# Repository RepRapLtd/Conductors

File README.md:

# Conductors
Experiments with 3D printing conducting filament

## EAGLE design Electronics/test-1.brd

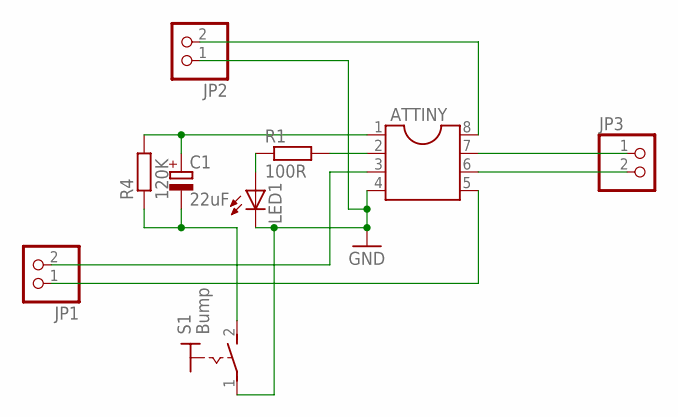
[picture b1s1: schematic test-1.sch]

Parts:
ATTINY: DIL8; DIL08
C1: 22uF; E3,5-8
JP1, JP2, JP3: PINHD-1X2; 1X02
LED1: LED3MM
R1: 100R; 0204/7
R4: 120K; 0204/7
S1: Bump; MS243

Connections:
GND: ATTINY.4, JP2.1, LED1.K (C), S1.1
unnamed: ATTINY.2, R1.2
unnamed: LED1.A, R1.1
unnamed: ATTINY.3, JP1.2
unnamed: ATTINY.8, JP2.2
unnamed: ATTINY.5, JP1.1
unnamed: ATTINY.7, JP3.1
unnamed: ATTINY.6, JP3.2
unnamed: C1.-, R4.1, S1.2 (S)
RST: ATTINY.1, C1.+, R4.2

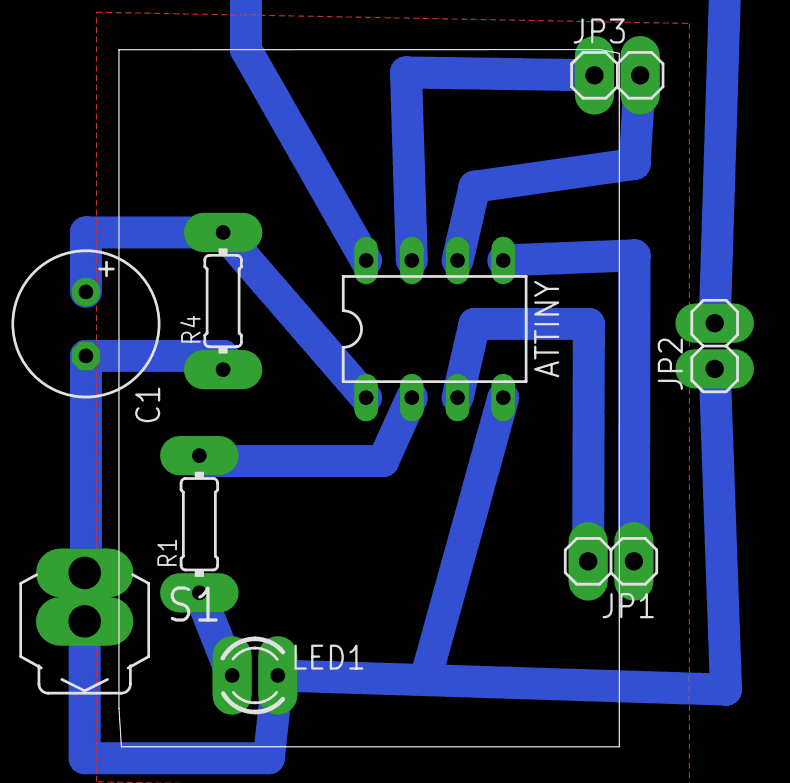
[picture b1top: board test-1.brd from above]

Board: 2 copper layers, 9 parts (0 on the bottom side), 10 nets.

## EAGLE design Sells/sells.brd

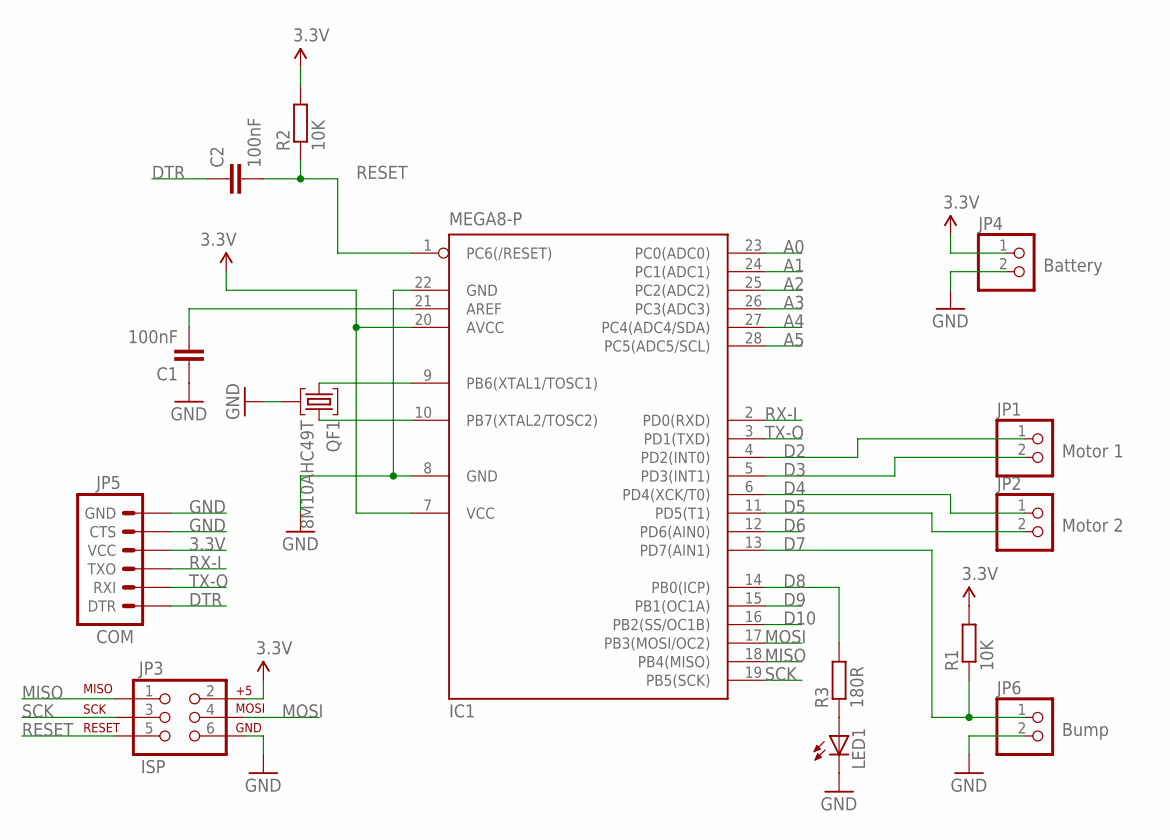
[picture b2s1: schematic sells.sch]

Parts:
C1, C2: 100nF; C050-050X075
IC1: MEGA8-P; DIL28-3
JP1, JP2, JP4, JP6: PINHD-1X2; 1X02
JP3: ISP; 2X3
JP5: COM; 1X06
LED1: LED3MM
QF1: 8M10AHC49T; HC49U
R1, R2: 10K; 0207/10
R3: 180R; 0207/10

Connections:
3.3V: IC1.7 (VCC), IC1.20 (AVCC), JP3.2, JP4.1, JP5.4 (VCC), R1.2, R2.2
A0: IC1.23 (PC0(ADC0))
A1: IC1.24 (PC1(ADC1))
A2: IC1.25 (PC2(ADC2))
A3: IC1.26 (PC3(ADC3))
A4: IC1.27 (PC4(ADC4/SDA))
A5: IC1.28 (PC5(ADC5/SCL))
D2: IC1.4 (PD2(INT0)), JP1.1
D3: IC1.5 (PD3(INT1)), JP1.2
D4: IC1.6 (PD4(XCK/T0)), JP2.1
D5: IC1.11 (PD5(T1)), JP2.2
D6: IC1.12 (PD6(AIN0))
D7: IC1.13 (PD7(AIN1)), JP6.1, R1.1
D8: IC1.14 (PB0(ICP)), R3.2
D9: IC1.15 (PB1(OC1A))
D10: IC1.16 (PB2(SS/OC1B))
DTR: C2.1, JP5.1 (DTR)
GND: C1.1, IC1.8 (GND), IC1.22 (GND), JP3.6, JP4.2, JP5.5 (CTS), JP5.6 (GND), JP6.2, LED1.K (C), QF1.2
MISO: IC1.18 (PB4(MISO)), JP3.1
MOSI: IC1.17 (PB3(MOSI/OC2)), JP3.4
unnamed: IC1.9 (PB6(XTAL1/TOSC1)), QF1.1
unnamed: IC1.10 (PB7(XTAL2/TOSC2)), QF1.3
unnamed: C1.2, IC1.21 (AREF)
unnamed: LED1.A, R3.1
RESET: C2.2, IC1.1 (PC6(/RESET)), JP3.5, R2.1
RX-I: IC1.2 (PD0(RXD)), JP5.3 (TXO)
SCK: IC1.19 (PB5(SCK)), JP3.3
TX-O: IC1.3 (PD1(TXD)), JP5.2 (RXI)

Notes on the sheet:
Battery
Motor 1
Motor 2
Bump

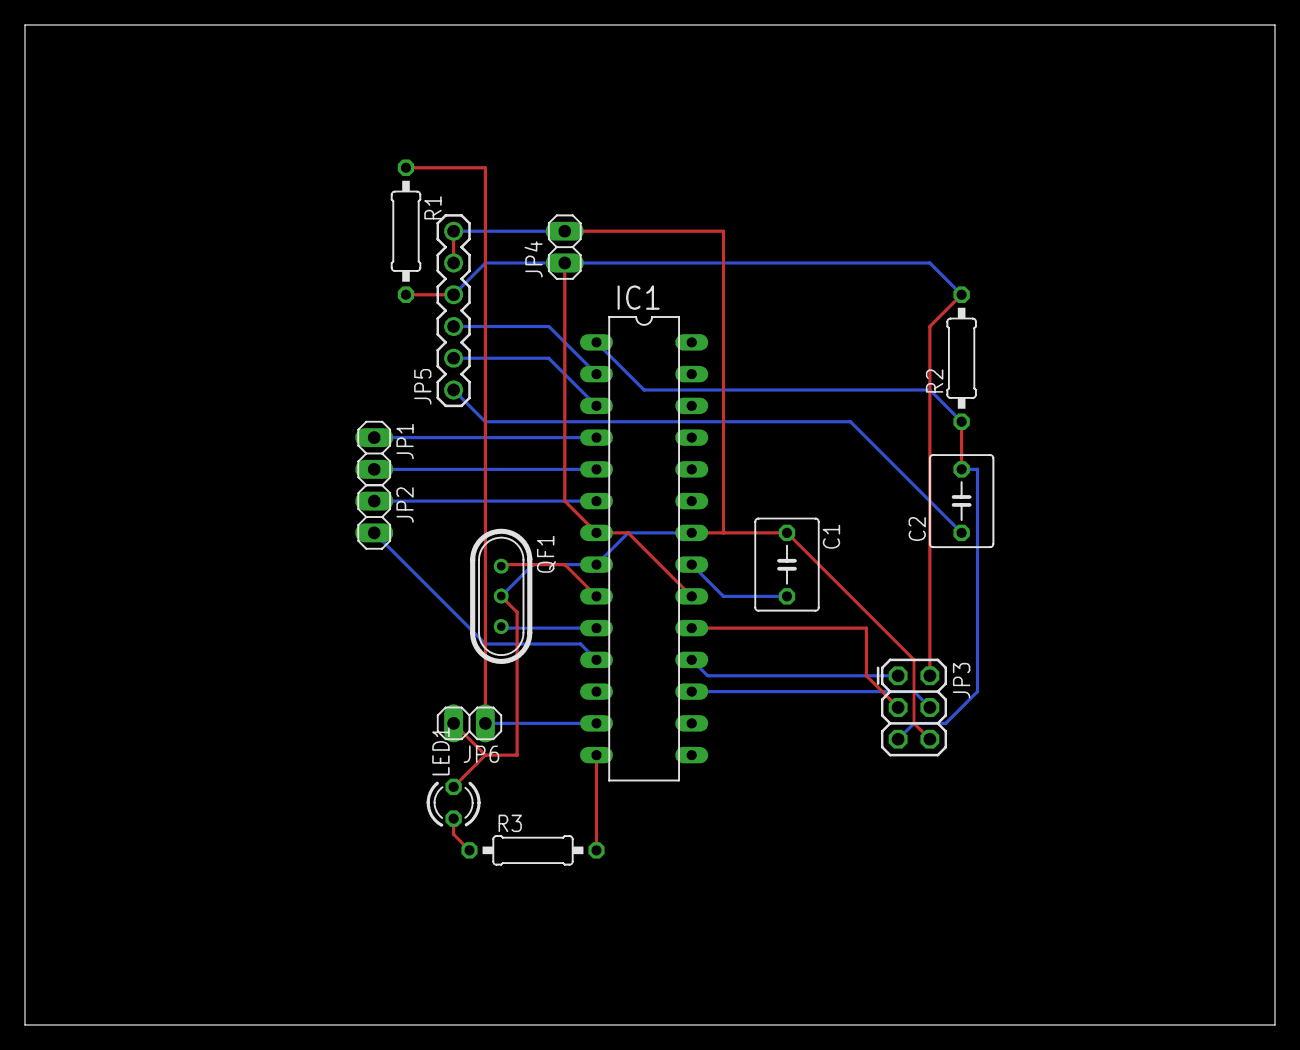
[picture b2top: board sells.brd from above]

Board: 2 copper layers, 100.0 x 80.0 mm, 14 parts (0 on the bottom side), 19 nets.

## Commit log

2022-07-16 FreeCAD Python program to create FFF printable electronics.
2022-07-19 Test print of chip holder.
2022-07-20 Further work on the Python track creating program.
2022-07-21 First attempt (not wholly successful) at laying down multiple tracks...
2022-07-25 Further work on test circuit.
2024-05-29 Bringing up to date.
2024-05-29 Updating

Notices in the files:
parts and their libraries:
SparkFun: Licensing: CC v3.0 Share-Alike You are welcome to use this library for commercial purposes.
